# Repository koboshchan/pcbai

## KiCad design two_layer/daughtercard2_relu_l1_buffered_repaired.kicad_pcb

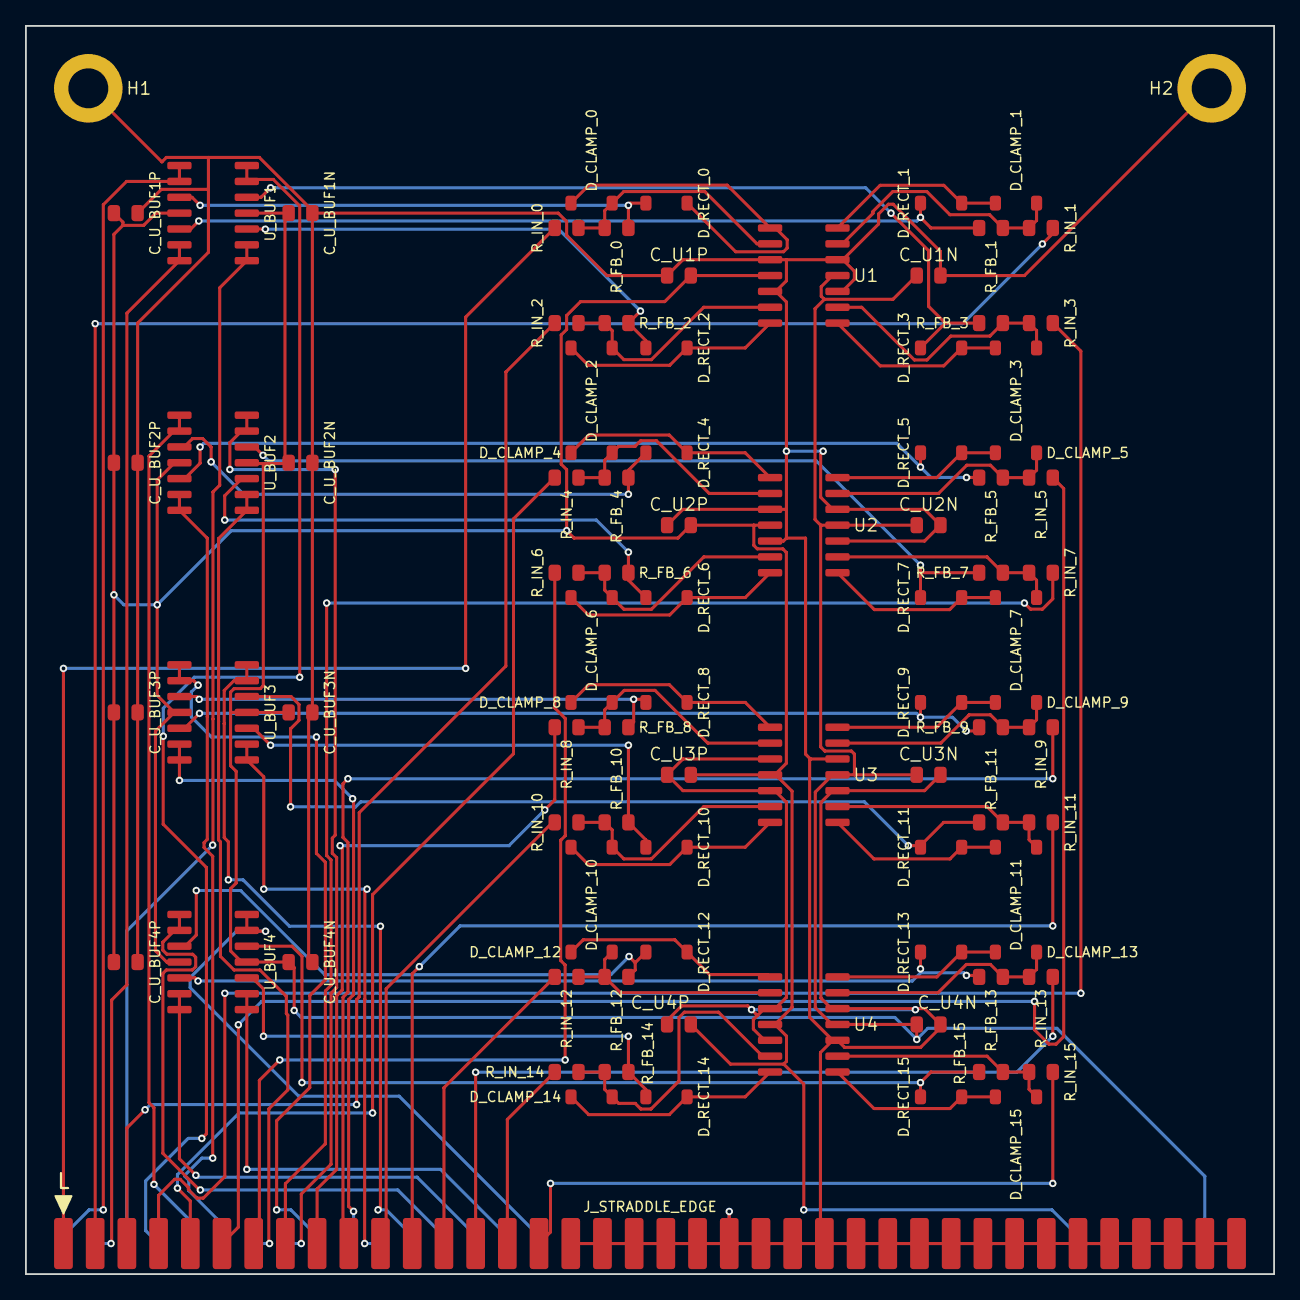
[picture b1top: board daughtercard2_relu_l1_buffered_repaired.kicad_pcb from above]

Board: 2 copper layers, 100.0 x 100.0 mm, 91 parts (0 on the bottom side), 83 nets.

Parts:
C_U1N, C_U1P, C_U2N, C_U2P, C_U3N, C_U3P, C_U4N, C_U4P: 0.1uF; C_0805_2012Metric
C_U_BUF1N, C_U_BUF1P, C_U_BUF2N, C_U_BUF2P, C_U_BUF3N, C_U_BUF3P, C_U_BUF4N, C_U_BUF4P: 0.1uF; C_0805_2012Metric
D_CLAMP_0, D_CLAMP_1, D_CLAMP_2, D_CLAMP_3, D_CLAMP_4, D_CLAMP_5, D_CLAMP_6, D_CLAMP_7, D_CLAMP_8, D_CLAMP_9, D_CLAMP_10, D_CLAMP_11, D_CLAMP_12, D_CLAMP_13, D_CLAMP_14, D_CLAMP_15: 1N4148W; D_SOD-123
D_RECT_0, D_RECT_1, D_RECT_2, D_RECT_3, D_RECT_4, D_RECT_5, D_RECT_6, D_RECT_7, D_RECT_8, D_RECT_9, D_RECT_10, D_RECT_11, D_RECT_12, D_RECT_13, D_RECT_14, D_RECT_15: 1N4148W; D_SOD-123
H1, H2: MountingHole; MountingHole_3.2mm_M3_Pad
J_STRADDLE_EDGE: PinHeader_2x38_Straddle; PinHeader_2x38_Straddle_P2.54mm
R_FB_0, R_FB_1, R_FB_2, R_FB_3, R_FB_4, R_FB_5, R_FB_6, R_FB_7, R_FB_8, R_FB_9, R_FB_10, R_FB_11, R_FB_12, R_FB_13, R_FB_14, R_FB_15: 10k; R_0805_2012Metric
R_IN_0, R_IN_1, R_IN_2, R_IN_3, R_IN_4, R_IN_5, R_IN_6, R_IN_7, R_IN_8, R_IN_9, R_IN_10, R_IN_11, R_IN_12, R_IN_13, R_IN_14, R_IN_15: 10k; R_0805_2012Metric
U1, U2, U3, U4: TL074; SOIC-14_3.9x8.7mm_P1.27mm
U_BUF1, U_BUF2, U_BUF3, U_BUF4: TL074; SOIC-14_3.9x8.7mm_P1.27mm

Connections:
+15V: C_U1P.2, C_U2P.2, C_U3P.2, C_U4P.2, C_U_BUF1P.1, C_U_BUF2P.1, C_U_BUF3P.1, C_U_BUF4P.1, J_STRADDLE_EDGE.B33, J_STRADDLE_EDGE.B34, U1.4, U2.4, U3.4, U4.4, U_BUF1.4, U_BUF2.4, U_BUF3.4, U_BUF4.4
-15V: C_U1N.1, C_U2N.1, C_U3N.1, C_U4N.1, C_U_BUF1N.1, C_U_BUF2N.1, C_U_BUF3N.1, C_U_BUF4N.1, J_STRADDLE_EDGE.B37, J_STRADDLE_EDGE.B38, U1.11, U2.11, U3.11, U4.11, U_BUF1.11, U_BUF2.11, U_BUF3.11, U_BUF4.11
ACT_0: J_STRADDLE_EDGE.B1, U_BUF1.1, U_BUF1.2
ACT_1: J_STRADDLE_EDGE.B2, U_BUF1.6, U_BUF1.7
ACT_2: J_STRADDLE_EDGE.B3, U_BUF1.8, U_BUF1.9
ACT_3: J_STRADDLE_EDGE.B4, U_BUF1.13, U_BUF1.14
ACT_4: J_STRADDLE_EDGE.B5, U_BUF2.1, U_BUF2.2
ACT_5: J_STRADDLE_EDGE.B6, U_BUF2.6, U_BUF2.7
ACT_6: J_STRADDLE_EDGE.B7, U_BUF2.8, U_BUF2.9
ACT_7: J_STRADDLE_EDGE.B8, U_BUF2.13, U_BUF2.14
ACT_8: J_STRADDLE_EDGE.B9, U_BUF3.1, U_BUF3.2
ACT_9: J_STRADDLE_EDGE.B10, U_BUF3.6, U_BUF3.7
ACT_10: J_STRADDLE_EDGE.B11, U_BUF3.8, U_BUF3.9
ACT_11: J_STRADDLE_EDGE.B12, U_BUF3.13, U_BUF3.14
ACT_12: J_STRADDLE_EDGE.B13, U_BUF4.1, U_BUF4.2
ACT_13: J_STRADDLE_EDGE.B14, U_BUF4.6, U_BUF4.7
ACT_14: J_STRADDLE_EDGE.B15, U_BUF4.8, U_BUF4.9
ACT_15: J_STRADDLE_EDGE.B16, U_BUF4.13, U_BUF4.14
GND: C_U1N.2, C_U1P.1, C_U2N.2, C_U2P.1, C_U3N.2, C_U3P.1, C_U4N.2, C_U4P.1, C_U_BUF1N.2, C_U_BUF1P.2, C_U_BUF2N.2, C_U_BUF2P.2, C_U_BUF3N.2, C_U_BUF3P.2, C_U_BUF4N.2, C_U_BUF4P.2, H1.1, H2.1, J_STRADDLE_EDGE.A17, J_STRADDLE_EDGE.A18, J_STRADDLE_EDGE.A19, J_STRADDLE_EDGE.A20, J_STRADDLE_EDGE.A21, J_STRADDLE_EDGE.A22, J_STRADDLE_EDGE.A23, J_STRADDLE_EDGE.A24, J_STRADDLE_EDGE.A25, J_STRADDLE_EDGE.A26, J_STRADDLE_EDGE.A27, J_STRADDLE_EDGE.A28, J_STRADDLE_EDGE.A29, J_STRADDLE_EDGE.A30, J_STRADDLE_EDGE.A31, J_STRADDLE_EDGE.A32, J_STRADDLE_EDGE.A33, J_STRADDLE_EDGE.A34, J_STRADDLE_EDGE.A35, J_STRADDLE_EDGE.A36, J_STRADDLE_EDGE.A37, J_STRADDLE_EDGE.A38, J_STRADDLE_EDGE.B17, J_STRADDLE_EDGE.B18, J_STRADDLE_EDGE.B19, J_STRADDLE_EDGE.B20, J_STRADDLE_EDGE.B21, J_STRADDLE_EDGE.B22, J_STRADDLE_EDGE.B23, J_STRADDLE_EDGE.B24, J_STRADDLE_EDGE.B25, J_STRADDLE_EDGE.B26, J_STRADDLE_EDGE.B27, J_STRADDLE_EDGE.B28, J_STRADDLE_EDGE.B29, J_STRADDLE_EDGE.B30, J_STRADDLE_EDGE.B31, J_STRADDLE_EDGE.B32, U1.3, U1.5, U1.10, U1.12, U2.3, U2.5, U2.10, U2.12, U3.3, U3.5, U3.10, U3.12, U4.3, U4.5, U4.10, U4.12
INV_RELU_0: D_CLAMP_0.2, R_FB_0.1, R_IN_0.2, U1.2
INV_RELU_1: D_CLAMP_1.2, R_FB_1.2, R_IN_1.1, U1.13
INV_RELU_2: D_CLAMP_2.2, R_FB_2.1, R_IN_2.2, U1.6
INV_RELU_3: D_CLAMP_3.2, R_FB_3.2, R_IN_3.1, U1.9
INV_RELU_4: D_CLAMP_4.2, R_FB_4.1, R_IN_4.2, U2.2
INV_RELU_5: D_CLAMP_5.2, R_FB_5.2, R_IN_5.1, U2.13
INV_RELU_6: D_CLAMP_6.2, R_FB_6.1, R_IN_6.2, U2.6
INV_RELU_7: D_CLAMP_7.2, R_FB_7.2, R_IN_7.1, U2.9
INV_RELU_8: D_CLAMP_8.2, R_FB_8.1, R_IN_8.2, U3.2
INV_RELU_9: D_CLAMP_9.2, R_FB_9.2, R_IN_9.1, U3.13
INV_RELU_10: D_CLAMP_10.2, R_FB_10.1, R_IN_10.2, U3.6
INV_RELU_11: D_CLAMP_11.2, R_FB_11.2, R_IN_11.1, U3.9
INV_RELU_12: D_CLAMP_12.2, R_FB_12.1, R_IN_12.2, U4.2
INV_RELU_13: D_CLAMP_13.2, R_FB_13.2, R_IN_13.1, U4.13
INV_RELU_14: D_CLAMP_14.2, R_FB_14.1, R_IN_14.2, U4.6
INV_RELU_15: D_CLAMP_15.2, R_FB_15.2, R_IN_15.1, U4.9
OP_OUT_0: D_CLAMP_0.1, D_RECT_0.2, U1.1
OP_OUT_1: D_CLAMP_1.1, D_RECT_1.2, U1.14
OP_OUT_2: D_CLAMP_2.1, D_RECT_2.2, U1.7
OP_OUT_3: D_CLAMP_3.1, D_RECT_3.2, U1.8
OP_OUT_4: D_CLAMP_4.1, D_RECT_4.2, U2.1
OP_OUT_5: D_CLAMP_5.1, D_RECT_5.2, U2.14
OP_OUT_6: D_CLAMP_6.1, D_RECT_6.2, U2.7
OP_OUT_7: D_CLAMP_7.1, D_RECT_7.2, U2.8
OP_OUT_8: D_CLAMP_8.1, D_RECT_8.2, U3.1
OP_OUT_9: D_CLAMP_9.1, D_RECT_9.2, U3.14
OP_OUT_10: D_CLAMP_10.1, D_RECT_10.2, U3.7
OP_OUT_11: D_CLAMP_11.1, D_RECT_11.2, U3.8
OP_OUT_12: D_CLAMP_12.1, D_RECT_12.2, U4.1
OP_OUT_13: D_CLAMP_13.1, D_RECT_13.2, U4.14
OP_OUT_14: D_CLAMP_14.1, D_RECT_14.2, U4.7
OP_OUT_15: D_CLAMP_15.1, D_RECT_15.2, U4.8
RECT_0: D_RECT_0.1, R_FB_0.2, U_BUF1.3
RECT_1: D_RECT_1.1, R_FB_1.1, U_BUF1.5
RECT_2: D_RECT_2.1, R_FB_2.2, U_BUF1.10
RECT_3: D_RECT_3.1, R_FB_3.1, U_BUF1.12
RECT_4: D_RECT_4.1, R_FB_4.2, U_BUF2.3
RECT_5: D_RECT_5.1, R_FB_5.1, U_BUF2.5
RECT_6: D_RECT_6.1, R_FB_6.2, U_BUF2.10
RECT_7: D_RECT_7.1, R_FB_7.1, U_BUF2.12
RECT_8: D_RECT_8.1, R_FB_8.2, U_BUF3.3
RECT_9: D_RECT_9.1, R_FB_9.1, U_BUF3.5
RECT_10: D_RECT_10.1, R_FB_10.2, U_BUF3.10
RECT_11: D_RECT_11.1, R_FB_11.1, U_BUF3.12
RECT_12: D_RECT_12.1, R_FB_12.2, U_BUF4.3
RECT_13: D_RECT_13.1, R_FB_13.1, U_BUF4.5
RECT_14: D_RECT_14.1, R_FB_14.2, U_BUF4.10
RECT_15: D_RECT_15.1, R_FB_15.1, U_BUF4.12
V_SUM_0: J_STRADDLE_EDGE.A1, R_IN_0.1
V_SUM_1: J_STRADDLE_EDGE.A2, R_IN_1.2
V_SUM_2: J_STRADDLE_EDGE.A3, R_IN_2.1
V_SUM_3: J_STRADDLE_EDGE.A4, R_IN_3.2
V_SUM_4: J_STRADDLE_EDGE.A5, R_IN_4.1
V_SUM_5: J_STRADDLE_EDGE.A6, R_IN_5.2
V_SUM_6: J_STRADDLE_EDGE.A7, R_IN_6.1
V_SUM_7: J_STRADDLE_EDGE.A8, R_IN_7.2
V_SUM_8: J_STRADDLE_EDGE.A9, R_IN_8.1
V_SUM_9: J_STRADDLE_EDGE.A10, R_IN_9.2
V_SUM_10: J_STRADDLE_EDGE.A11, R_IN_10.1
V_SUM_11: J_STRADDLE_EDGE.A12, R_IN_11.2
V_SUM_12: J_STRADDLE_EDGE.A13, R_IN_12.1
V_SUM_13: J_STRADDLE_EDGE.A14, R_IN_13.2
V_SUM_14: J_STRADDLE_EDGE.A15, R_IN_14.1
V_SUM_15: J_STRADDLE_EDGE.A16, R_IN_15.2

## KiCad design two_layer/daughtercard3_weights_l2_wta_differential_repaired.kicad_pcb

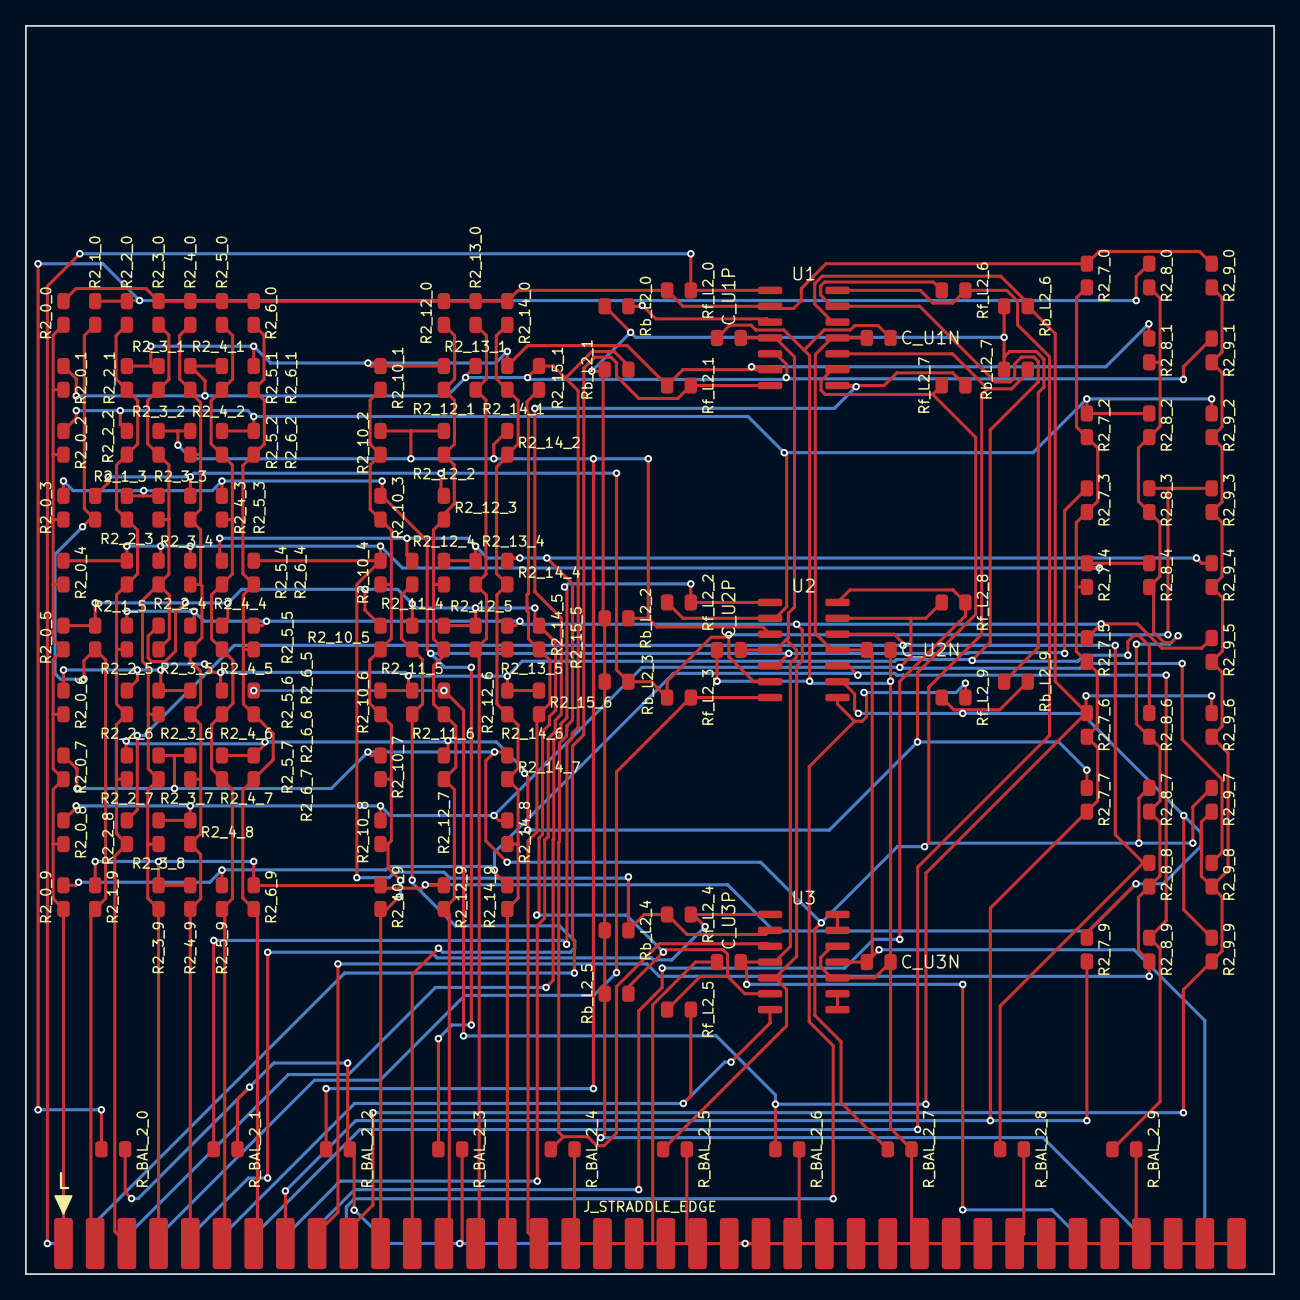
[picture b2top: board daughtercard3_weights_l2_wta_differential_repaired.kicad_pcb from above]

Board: 2 copper layers, 100.0 x 100.0 mm, 163 parts (0 on the bottom side), 52 nets.

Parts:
C_U1N, C_U1P, C_U2N, C_U2P, C_U3N, C_U3P: 0.1uF; C_0805_2012Metric
J_STRADDLE_EDGE: PinHeader_2x38_Straddle; PinHeader_2x38_Straddle_P2.54mm
R2_0_0, R2_3_2, R2_8_3, R2_9_1, R2_10_6: 91k; R_0805_2012Metric
R2_0_1, R2_3_0, R2_6_5, R2_7_4, R2_9_0, R2_14_1: 100k; R_0805_2012Metric
R2_0_2: 1.6M; R_0805_2012Metric
R2_0_3, R2_1_3, R2_5_4, R2_6_2, R2_7_6, R2_10_5, R2_10_8, R2_13_0, R2_14_0: 220k; R_0805_2012Metric
R2_0_4, R2_2_7, R2_5_3, R2_7_3, R2_8_6, R2_9_3, R2_13_5: 270k; R_0805_2012Metric
R2_0_5, R2_0_6, R2_5_0: 56k; R_0805_2012Metric
R2_0_7, R2_3_5: 470k; R_0805_2012Metric
R2_0_8, R2_1_9, R2_5_5, R2_5_9, R2_9_2, R2_9_4, R2_9_8, R2_10_7, R2_11_4, R2_11_6, R2_12_6: 180k; R_0805_2012Metric
R2_0_9, R2_2_2, R2_4_5, R2_4_6, R2_8_9, R2_12_5, R2_14_9: 300k; R_0805_2012Metric
R2_1_0, R2_2_3, R2_2_4, R2_8_0, R2_10_3, R2_11_5, R2_14_7, R2_15_5: 240k; R_0805_2012Metric
R2_1_5, R2_5_1: 82k; R_0805_2012Metric
R2_2_0, R2_10_9, R2_14_8: 110k; R_0805_2012Metric
R2_2_1: 51k; R_0805_2012Metric
R2_2_5, R2_3_3, R2_3_7, R2_15_6: 360k; R_0805_2012Metric
R2_2_6, R2_4_9: 430k; R_0805_2012Metric
R2_2_8: 5.1M; R_0805_2012Metric
R2_3_1, R2_6_9, R2_7_7, R2_9_9, R2_10_2, R2_13_4: 150k; R_0805_2012Metric
R2_3_4, R2_3_9, R2_5_2, R2_14_4: 130k; R_0805_2012Metric
R2_3_6, R2_5_6, R2_6_4, R2_7_2, R2_7_5, R2_10_1: 68k; R_0805_2012Metric
R2_3_8, R2_5_7, R2_6_0, R2_6_6, R2_8_2, R2_12_1, R2_12_4, R2_14_6: 200k; R_0805_2012Metric
R2_4_0, R2_9_5: 1M; R_0805_2012Metric
R2_4_1, R2_4_4, R2_8_8: 120k; R_0805_2012Metric
R2_4_2: 680k; R_0805_2012Metric
R2_4_3, R2_14_2: 750k; R_0805_2012Metric
R2_4_7, R2_12_3: 390k; R_0805_2012Metric
R2_4_8: 62k; R_0805_2012Metric
R2_6_1, R2_12_7: 43k; R_0805_2012Metric
R2_6_7, R2_8_7: 330k; R_0805_2012Metric
R2_7_0, R2_7_9: 75k; R_0805_2012Metric
R2_8_1, R2_12_9, R2_15_1: 160k; R_0805_2012Metric
R2_8_4, R2_9_6, R2_9_7: 620k; R_0805_2012Metric
R2_10_4: 33k; R_0805_2012Metric
R2_12_0: 510k; R_0805_2012Metric
R2_12_2: 1.1M; R_0805_2012Metric
R2_13_1: 820k; R_0805_2012Metric
R2_14_5: 2.7M; R_0805_2012Metric
R_BAL_2_0: 14.7k; R_0805_2012Metric
R_BAL_2_1: 24.9k; R_0805_2012Metric
R_BAL_2_2: 35.7k; R_0805_2012Metric
R_BAL_2_3: 61.9k; R_0805_2012Metric
R_BAL_2_4: 17.4k; R_0805_2012Metric
R_BAL_2_5: 28k; R_0805_2012Metric
R_BAL_2_6: 14.3k; R_0805_2012Metric
R_BAL_2_7: 34k; R_0805_2012Metric
R_BAL_2_8: 21k; R_0805_2012Metric
R_BAL_2_9: 18.2k; R_0805_2012Metric
Rb_L2_0: 270k; R_0805_2012Metric
Rb_L2_1, Rb_L2_3: 160k; R_0805_2012Metric
Rb_L2_2, Rb_L2_4: 560k; R_0805_2012Metric
Rb_L2_5: 2M; R_0805_2012Metric
Rb_L2_6: 240k; R_0805_2012Metric
Rb_L2_7: 3.9M; R_0805_2012Metric
Rb_L2_9: 360k; R_0805_2012Metric
Rf_L2_0, Rf_L2_1, Rf_L2_2, Rf_L2_3, Rf_L2_4, Rf_L2_5, Rf_L2_6, Rf_L2_7, Rf_L2_8, Rf_L2_9: 100k; R_0805_2012Metric
U1, U2, U3: TL074; SOIC-14_3.9x8.7mm_P1.27mm

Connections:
+5V_REF: J_STRADDLE_EDGE.B35, Rb_L2_0.1, Rb_L2_1.1, Rb_L2_2.1, Rb_L2_3.1, Rb_L2_4.1, Rb_L2_5.1, Rb_L2_6.1, Rb_L2_7.1, Rb_L2_9.1
+15V: C_U1P.2, C_U2P.2, C_U3P.2, J_STRADDLE_EDGE.B33, J_STRADDLE_EDGE.B34, U1.4, U2.4, U3.4
-15V: C_U1N.1, C_U2N.1, C_U3N.1, J_STRADDLE_EDGE.B37, J_STRADDLE_EDGE.B38, U1.11, U2.11, U3.11
ACT_0: J_STRADDLE_EDGE.A1, R2_0_0.1, R2_0_1.1, R2_0_2.1, R2_0_3.1, R2_0_4.1, R2_0_5.1, R2_0_6.1, R2_0_7.1, R2_0_8.1, R2_0_9.1
ACT_1: J_STRADDLE_EDGE.A2, R2_1_0.1, R2_1_3.1, R2_1_5.1, R2_1_9.1
ACT_2: J_STRADDLE_EDGE.A3, R2_2_0.1, R2_2_1.1, R2_2_2.1, R2_2_3.1, R2_2_4.1, R2_2_5.1, R2_2_6.1, R2_2_7.1, R2_2_8.1
ACT_3: J_STRADDLE_EDGE.A4, R2_3_0.1, R2_3_1.1, R2_3_2.1, R2_3_3.1, R2_3_4.1, R2_3_5.1, R2_3_6.1, R2_3_7.1, R2_3_8.1, R2_3_9.1
ACT_4: J_STRADDLE_EDGE.A5, R2_4_0.1, R2_4_1.1, R2_4_2.1, R2_4_3.1, R2_4_4.1, R2_4_5.1, R2_4_6.1, R2_4_7.1, R2_4_8.1, R2_4_9.1
ACT_5: J_STRADDLE_EDGE.A6, R2_5_0.1, R2_5_1.1, R2_5_2.1, R2_5_3.1, R2_5_4.1, R2_5_5.1, R2_5_6.1, R2_5_7.1, R2_5_9.1
ACT_6: J_STRADDLE_EDGE.A7, R2_6_0.1, R2_6_1.1, R2_6_2.1, R2_6_4.1, R2_6_5.1, R2_6_6.1, R2_6_7.1, R2_6_9.1
ACT_7: J_STRADDLE_EDGE.A8, R2_7_0.1, R2_7_2.1, R2_7_3.1, R2_7_4.1, R2_7_5.1, R2_7_6.1, R2_7_7.1, R2_7_9.1
ACT_8: J_STRADDLE_EDGE.A9, R2_8_0.1, R2_8_1.1, R2_8_2.1, R2_8_3.1, R2_8_4.1, R2_8_6.1, R2_8_7.1, R2_8_8.1, R2_8_9.1
ACT_9: J_STRADDLE_EDGE.A10, R2_9_0.1, R2_9_1.1, R2_9_2.1, R2_9_3.1, R2_9_4.1, R2_9_5.1, R2_9_6.1, R2_9_7.1, R2_9_8.1, R2_9_9.1
ACT_10: J_STRADDLE_EDGE.A11, R2_10_1.1, R2_10_2.1, R2_10_3.1, R2_10_4.1, R2_10_5.1, R2_10_6.1, R2_10_7.1, R2_10_8.1, R2_10_9.1
ACT_11: J_STRADDLE_EDGE.A12, R2_11_4.1, R2_11_5.1, R2_11_6.1
ACT_12: J_STRADDLE_EDGE.A13, R2_12_0.1, R2_12_1.1, R2_12_2.1, R2_12_3.1, R2_12_4.1, R2_12_5.1, R2_12_6.1, R2_12_7.1, R2_12_9.1
ACT_13: J_STRADDLE_EDGE.A14, R2_13_0.1, R2_13_1.1, R2_13_4.1, R2_13_5.1
ACT_14: J_STRADDLE_EDGE.A15, R2_14_0.1, R2_14_1.1, R2_14_2.1, R2_14_4.1, R2_14_5.1, R2_14_6.1, R2_14_7.1, R2_14_8.1, R2_14_9.1
ACT_15: J_STRADDLE_EDGE.A16, R2_15_1.1, R2_15_5.1, R2_15_6.1
GND: C_U1N.2, C_U1P.1, C_U2N.2, C_U2P.1, C_U3N.2, C_U3P.1, J_STRADDLE_EDGE.A17, J_STRADDLE_EDGE.A18, J_STRADDLE_EDGE.A19, J_STRADDLE_EDGE.A20, J_STRADDLE_EDGE.A21, J_STRADDLE_EDGE.A22, J_STRADDLE_EDGE.A23, J_STRADDLE_EDGE.A24, J_STRADDLE_EDGE.A25, J_STRADDLE_EDGE.A26, J_STRADDLE_EDGE.A27, J_STRADDLE_EDGE.A28, J_STRADDLE_EDGE.A29, J_STRADDLE_EDGE.A30, J_STRADDLE_EDGE.A31, J_STRADDLE_EDGE.A32, J_STRADDLE_EDGE.A33, J_STRADDLE_EDGE.A34, J_STRADDLE_EDGE.A35, J_STRADDLE_EDGE.A36, J_STRADDLE_EDGE.A37, J_STRADDLE_EDGE.A38, J_STRADDLE_EDGE.B11, J_STRADDLE_EDGE.B12, J_STRADDLE_EDGE.B13, J_STRADDLE_EDGE.B14, J_STRADDLE_EDGE.B15, J_STRADDLE_EDGE.B16, J_STRADDLE_EDGE.B17, J_STRADDLE_EDGE.B18, J_STRADDLE_EDGE.B19, J_STRADDLE_EDGE.B20, J_STRADDLE_EDGE.B21, J_STRADDLE_EDGE.B22, J_STRADDLE_EDGE.B23, J_STRADDLE_EDGE.B24, J_STRADDLE_EDGE.B25, J_STRADDLE_EDGE.B26, J_STRADDLE_EDGE.B27, J_STRADDLE_EDGE.B28, J_STRADDLE_EDGE.B29, J_STRADDLE_EDGE.B30, J_STRADDLE_EDGE.B31, J_STRADDLE_EDGE.B32, R_BAL_2_0.2, R_BAL_2_1.2, R_BAL_2_2.2, R_BAL_2_3.2, R_BAL_2_4.2, R_BAL_2_5.2, R_BAL_2_6.2, R_BAL_2_7.2, R_BAL_2_8.2, R_BAL_2_9.2, U3.10, U3.12
INV_L2_0: R2_0_0.2, R2_3_0.2, R2_4_0.2, R2_5_0.2, R2_6_0.2, R2_7_0.2, R2_9_0.2, R2_12_0.2, R2_13_0.2, R2_14_0.2, Rf_L2_0.1, U1.2
INV_L2_1: R2_2_1.2, R2_3_1.2, R2_6_1.2, R2_8_1.2, R2_10_1.2, R2_12_1.2, R2_14_1.2, Rf_L2_1.1, U1.6
INV_L2_2: R2_0_2.2, R2_2_2.2, R2_5_2.2, R2_6_2.2, R2_7_2.2, R2_8_2.2, R2_9_2.2, Rf_L2_2.1, U2.2
INV_L2_3: R2_1_3.2, R2_4_3.2, R2_8_3.2, R2_9_3.2, R2_12_3.2, Rb_L2_3.2, Rf_L2_3.1, U2.6
INV_L2_4: R2_0_4.2, R2_2_4.2, R2_3_4.2, R2_4_4.2, R2_6_4.2, R2_7_4.2, R2_8_4.2, R2_10_4.2, Rb_L2_4.2, Rf_L2_4.1, U3.2
INV_L2_5: R2_0_5.2, R2_1_5.2, R2_3_5.2, R2_5_5.2, R2_10_5.2, R2_11_5.2, R2_12_5.2, R2_13_5.2, R2_15_5.2, Rb_L2_5.2, Rf_L2_5.1, U3.6
INV_L2_6: R2_0_6.2, R2_2_6.2, R2_3_6.2, R2_4_6.2, R2_5_6.2, R2_8_6.2, R2_10_6.2, R2_11_6.2, R2_14_6.2, R2_15_6.2, Rf_L2_6.1, U1.13
INV_L2_7: R2_2_7.2, R2_5_7.2, R2_6_7.2, R2_7_7.2, R2_12_7.2, Rf_L2_7.1, U1.9
INV_L2_8: R2_0_8.2, R2_3_8.2, R2_4_8.2, R2_9_8.2, R2_10_8.2, R2_14_8.2, Rf_L2_8.1, U2.13
INV_L2_9: R2_1_9.2, R2_3_9.2, R2_4_9.2, R2_6_9.2, R2_7_9.2, R2_9_9.2, R2_10_9.2, R2_12_9.2, Rb_L2_9.2, Rf_L2_9.1, U2.9
NC_U3_8: U3.8, U3.9
NC_U3_14: U3.13, U3.14
POS_L2_0: R2_1_0.2, R2_2_0.2, R2_8_0.2, R_BAL_2_0.1, Rb_L2_0.2, U1.3
POS_L2_1: R2_0_1.2, R2_4_1.2, R2_5_1.2, R2_9_1.2, R2_13_1.2, R2_15_1.2, R_BAL_2_1.1, Rb_L2_1.2, U1.5
POS_L2_2: R2_3_2.2, R2_4_2.2, R2_10_2.2, R2_12_2.2, R2_14_2.2, R_BAL_2_2.1, Rb_L2_2.2, U2.3
POS_L2_3: R2_0_3.2, R2_2_3.2, R2_3_3.2, R2_5_3.2, R2_7_3.2, R2_10_3.2, R_BAL_2_3.1, U2.5
POS_L2_4: R2_5_4.2, R2_9_4.2, R2_11_4.2, R2_12_4.2, R2_13_4.2, R2_14_4.2, R_BAL_2_4.1, U3.3
POS_L2_5: R2_2_5.2, R2_4_5.2, R2_6_5.2, R2_7_5.2, R2_9_5.2, R2_14_5.2, R_BAL_2_5.1, U3.5
POS_L2_6: R2_6_6.2, R2_7_6.2, R2_9_6.2, R2_12_6.2, R_BAL_2_6.1, Rb_L2_6.2, U1.12
POS_L2_7: R2_0_7.2, R2_3_7.2, R2_4_7.2, R2_8_7.2, R2_9_7.2, R2_10_7.2, R2_14_7.2, R_BAL_2_7.1, Rb_L2_7.2, U1.10
POS_L2_8: R2_2_8.2, R2_8_8.2, R_BAL_2_8.1, U2.12
POS_L2_9: R2_0_9.2, R2_5_9.2, R2_8_9.2, R2_14_9.2, R_BAL_2_9.1, U2.10
SCORE_0: J_STRADDLE_EDGE.B1, Rf_L2_0.2, U1.1
SCORE_1: J_STRADDLE_EDGE.B2, Rf_L2_1.2, U1.7
SCORE_2: J_STRADDLE_EDGE.B3, Rf_L2_2.2, U2.1
SCORE_3: J_STRADDLE_EDGE.B4, Rf_L2_3.2, U2.7
SCORE_4: J_STRADDLE_EDGE.B5, Rf_L2_4.2, U3.1
SCORE_5: J_STRADDLE_EDGE.B6, Rf_L2_5.2, U3.7
SCORE_6: J_STRADDLE_EDGE.B7, Rf_L2_6.2, U1.14
SCORE_7: J_STRADDLE_EDGE.B8, Rf_L2_7.2, U1.8
SCORE_8: J_STRADDLE_EDGE.B9, Rf_L2_8.2, U2.14
SCORE_9: J_STRADDLE_EDGE.B10, Rf_L2_9.2, U2.8

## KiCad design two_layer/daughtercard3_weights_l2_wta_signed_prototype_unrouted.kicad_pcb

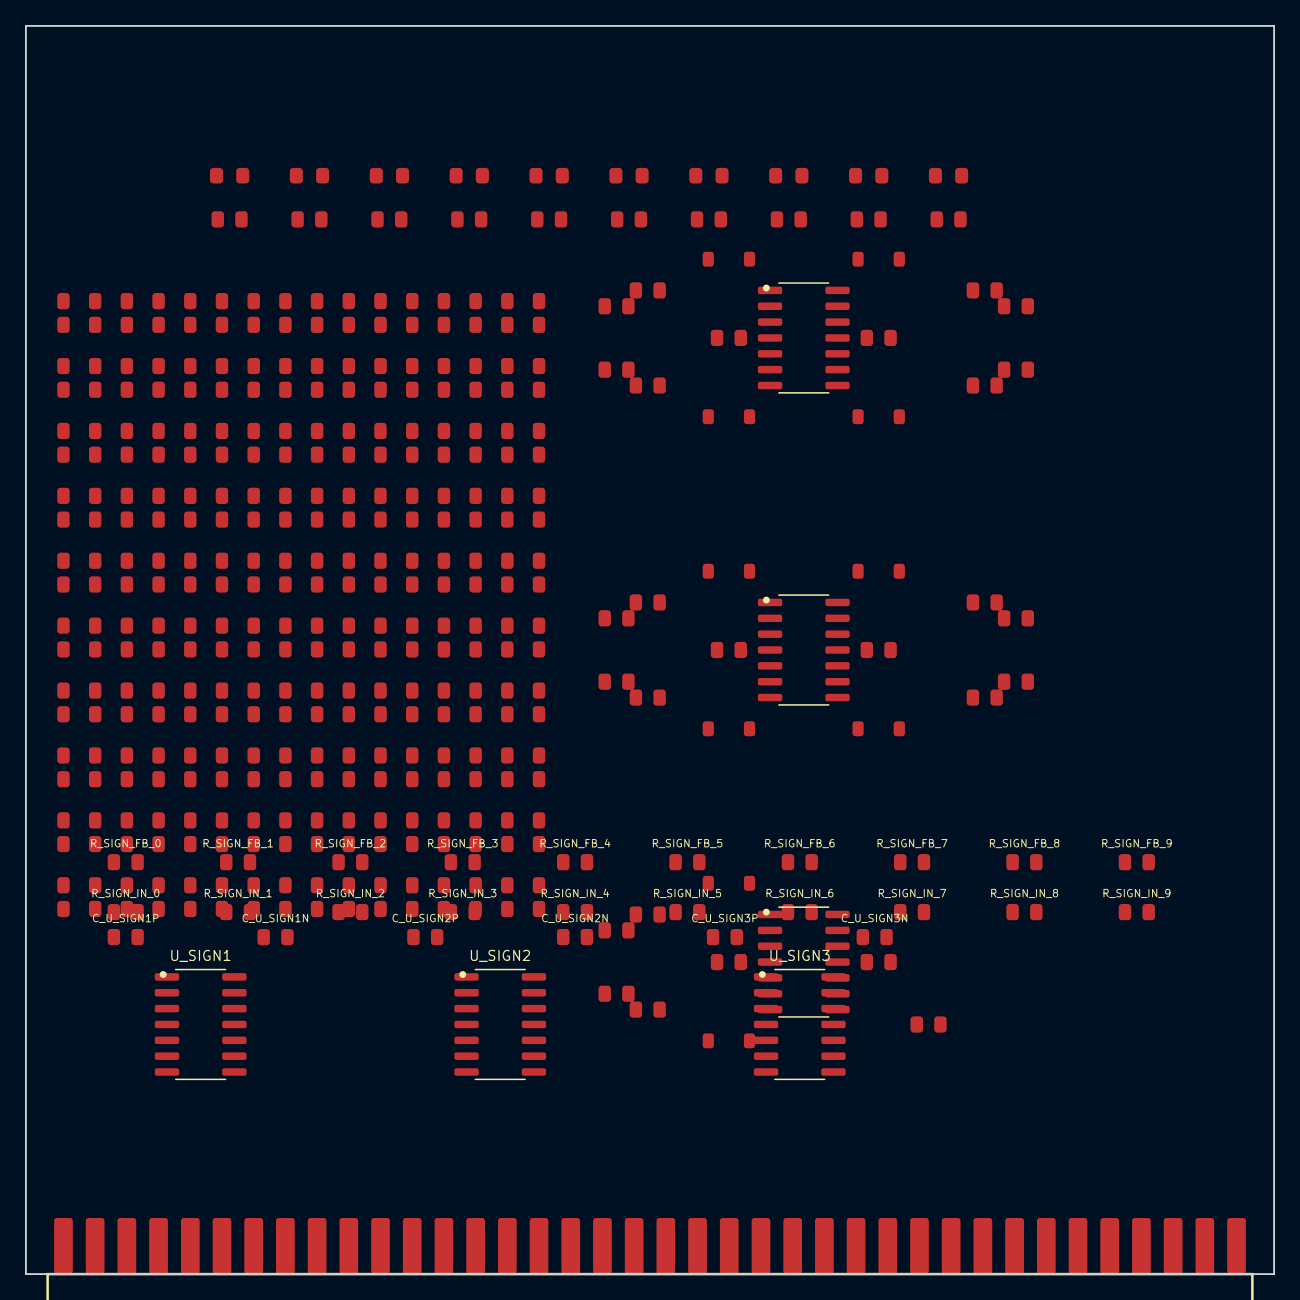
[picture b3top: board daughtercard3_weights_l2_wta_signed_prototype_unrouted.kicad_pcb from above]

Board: 2 copper layers, 100.0 x 100.0 mm, 250 parts (0 on the bottom side), 76 nets, no tracks yet.

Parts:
C_U1N, C_U1P, C_U2N, C_U2P, C_U3N, C_U3P: 0.1uF; C_0805_2012Metric
C_U_SIGN1N, C_U_SIGN1P, C_U_SIGN2N, C_U_SIGN2P, C_U_SIGN3N, C_U_SIGN3P: 0.1uF; C_0805_2012Metric
D_LED_0: Digit_0; LED_0805_2012Metric
D_LED_1: Digit_1; LED_0805_2012Metric
D_LED_2: Digit_2; LED_0805_2012Metric
D_LED_3: Digit_3; LED_0805_2012Metric
D_LED_4: Digit_4; LED_0805_2012Metric
D_LED_5: Digit_5; LED_0805_2012Metric
D_LED_6: Digit_6; LED_0805_2012Metric
D_LED_7: Digit_7; LED_0805_2012Metric
D_LED_8: Digit_8; LED_0805_2012Metric
D_LED_9: Digit_9; LED_0805_2012Metric
D_WTA_0, D_WTA_1, D_WTA_2, D_WTA_3, D_WTA_4, D_WTA_5, D_WTA_6, D_WTA_7, D_WTA_8, D_WTA_9: 1N4148; D_SOD-123
J_STRADDLE_EDGE: PinHeader_2x38_Straddle; PinHeader_2x38_Straddle_P2.54mm
R2_0_0, R2_0_1, R2_2_0, R2_3_2, R2_6_5, R2_7_0, R2_8_3, R2_8_8, R2_9_0, R2_10_9: 12k; R_0805_2012Metric
R2_0_2, R2_1_2, R2_1_7, R2_11_1, R2_15_2, R2_15_9: 300k; R_0805_2012Metric
R2_0_3, R2_0_7, R2_0_8, R2_0_9, R2_1_5, R2_2_2, R2_2_5, R2_2_6, R2_2_7, R2_4_7, R2_5_7, R2_7_3, R2_8_0, R2_8_7, R2_8_9, R2_9_6, R2_9_8, R2_12_5, R2_13_4, R2_14_6, R2_14_9: 33k; R_0805_2012Metric
R2_0_4, R2_2_3, R2_3_1, R2_3_4, R2_4_4, R2_4_5, R2_5_3, R2_5_5, R2_6_2, R2_6_9, R2_7_7, R2_8_2, R2_9_2, R2_10_3, R2_12_1, R2_12_4, R2_12_9, R2_14_7: 22k; R_0805_2012Metric
R2_0_5, R2_0_6, R2_2_1, R2_5_1, R2_5_6, R2_7_2, R2_7_5, R2_7_9: 7.5k; R_0805_2012Metric
R2_1_0, R2_1_6, R2_1_8, R2_2_8, R2_3_5, R2_4_2, R2_9_5, R2_11_2, R2_11_7, R2_11_9, R2_13_5, R2_13_6, R2_13_7, R2_15_3, R2_15_7, R2_15_8: 75k; R_0805_2012Metric
R2_1_1, R2_1_3, R2_1_9, R2_2_4, R2_10_5, R2_11_4, R2_14_0, R2_15_4: 51k; R_0805_2012Metric
R2_1_4, R2_2_9, R2_5_8, R2_8_4, R2_11_0, R2_11_5, R2_11_6, R2_11_8, R2_12_0, R2_12_8, R2_13_1, R2_13_8, R2_14_5, R2_15_0, R2_15_6: 100k; R_0805_2012Metric
R2_3_0, R2_4_1, R2_10_6, R2_14_1, R2_14_4, R2_14_8: 15k; R_0805_2012Metric
R2_3_3, R2_3_7, R2_3_8, R2_4_6, R2_6_6, R2_6_7, R2_7_1, R2_9_3, R2_10_8, R2_12_3, R2_13_2, R2_14_2: 43k; R_0805_2012Metric
R2_3_6, R2_4_8, R2_6_4, R2_7_4, R2_9_1, R2_10_1: 10k; R_0805_2012Metric
R2_3_9, R2_5_2, R2_5_4, R2_5_9, R2_7_6, R2_8_6, R2_10_7, R2_12_6: 20k; R_0805_2012Metric
R2_4_0, R2_4_3, R2_14_3: 390k; R_0805_2012Metric
R2_4_9, R2_7_8, R2_11_3, R2_12_2, R2_13_3, R2_13_9, R2_15_1: 200k; R_0805_2012Metric
R2_5_0, R2_6_1: 5.6k; R_0805_2012Metric
R2_6_0, R2_8_1, R2_9_4, R2_9_9, R2_10_2: 18k; R_0805_2012Metric
R2_6_3, R2_9_7: 47k; R_0805_2012Metric
R2_6_8, R2_13_0: 680k; R_0805_2012Metric
R2_8_5, R2_15_5: 1M; R_0805_2012Metric
R2_10_0: 10M; R_0805_2012Metric
R2_10_4: 3.3k; R_0805_2012Metric
R2_12_7: 5.1k; R_0805_2012Metric
R_LED_0, R_LED_1, R_LED_2, R_LED_3, R_LED_4, R_LED_5, R_LED_6, R_LED_7, R_LED_8, R_LED_9: 1k; R_0805_2012Metric
R_SIGN_FB_0, R_SIGN_FB_1, R_SIGN_FB_2, R_SIGN_FB_3, R_SIGN_FB_4, R_SIGN_FB_5, R_SIGN_FB_6, R_SIGN_FB_7, R_SIGN_FB_8, R_SIGN_FB_9: 1.2k; R_0805_2012Metric
R_SIGN_IN_0, R_SIGN_IN_1, R_SIGN_IN_2, R_SIGN_IN_3, R_SIGN_IN_4, R_SIGN_IN_5, R_SIGN_IN_6, R_SIGN_IN_7, R_SIGN_IN_8, R_SIGN_IN_9: 1.2k; R_0805_2012Metric
R_WTA: 10k; R_0805_2012Metric
Rb_L2_0, Rb_L2_6: 33k; R_0805_2012Metric
Rb_L2_1, Rb_L2_3: 18k; R_0805_2012Metric
Rb_L2_2, Rb_L2_4: 75k; R_0805_2012Metric
Rb_L2_5, Rb_L2_7: 100k; R_0805_2012Metric
Rb_L2_8: 470k; R_0805_2012Metric
Rb_L2_9: 43k; R_0805_2012Metric
Rf_L2_0, Rf_L2_1, Rf_L2_2, Rf_L2_3, Rf_L2_4, Rf_L2_5, Rf_L2_6, Rf_L2_7, Rf_L2_8, Rf_L2_9: 10k; R_0805_2012Metric
U1, U2, U3: TL074; SOIC-14_3.9x8.7mm_P1.27mm
U_SIGN1, U_SIGN2, U_SIGN3: TL074; SOIC-14_3.9x8.7mm_P1.27mm

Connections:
+5V_REF: J_STRADDLE_EDGE.B35, Rb_L2_3.1, Rb_L2_4.1, Rb_L2_5.1, Rb_L2_9.2
+12V: C_U1P.2, C_U2P.2, C_U3P.2, C_U_SIGN1P.1, C_U_SIGN2P.1, C_U_SIGN3P.1, J_STRADDLE_EDGE.B33, J_STRADDLE_EDGE.B34, U1.4, U2.4, U3.4, U_SIGN1.4, U_SIGN2.4, U_SIGN3.4
-5V_REF: J_STRADDLE_EDGE.B36, Rb_L2_0.1, Rb_L2_1.1, Rb_L2_2.1, Rb_L2_6.2, Rb_L2_7.2, Rb_L2_8.2
-12V: C_U1N.1, C_U2N.1, C_U3N.1, C_U_SIGN1N.1, C_U_SIGN2N.1, C_U_SIGN3N.1, J_STRADDLE_EDGE.B37, J_STRADDLE_EDGE.B38, R_WTA.2, U1.11, U2.11, U3.11, U_SIGN1.11, U_SIGN2.11, U_SIGN3.11
ACT_0: J_STRADDLE_EDGE.A1, R2_0_0.1, R2_0_1.1, R2_0_2.1, R2_0_3.1, R2_0_4.1, R2_0_5.1, R2_0_6.1, R2_0_7.1, R2_0_8.1, R2_0_9.1
ACT_1: J_STRADDLE_EDGE.A2, R2_1_0.1, R2_1_1.1, R2_1_2.1, R2_1_3.1, R2_1_4.1, R2_1_5.1, R2_1_6.1, R2_1_7.1, R2_1_8.1, R2_1_9.1
ACT_2: J_STRADDLE_EDGE.A3, R2_2_0.1, R2_2_1.1, R2_2_2.1, R2_2_3.1, R2_2_4.1, R2_2_5.1, R2_2_6.1, R2_2_7.1, R2_2_8.1, R2_2_9.1
ACT_3: J_STRADDLE_EDGE.A4, R2_3_0.1, R2_3_1.1, R2_3_2.1, R2_3_3.1, R2_3_4.1, R2_3_5.1, R2_3_6.1, R2_3_7.1, R2_3_8.1, R2_3_9.1
ACT_4: J_STRADDLE_EDGE.A5, R2_4_0.1, R2_4_1.1, R2_4_2.1, R2_4_3.1, R2_4_4.1, R2_4_5.1, R2_4_6.1, R2_4_7.1, R2_4_8.1, R2_4_9.1
ACT_5: J_STRADDLE_EDGE.A6, R2_5_0.1, R2_5_1.1, R2_5_2.1, R2_5_3.1, R2_5_4.1, R2_5_5.1, R2_5_6.1, R2_5_7.1, R2_5_8.1, R2_5_9.1
ACT_6: J_STRADDLE_EDGE.A7, R2_6_0.1, R2_6_1.1, R2_6_2.1, R2_6_3.1, R2_6_4.1, R2_6_5.1, R2_6_6.1, R2_6_7.1, R2_6_8.1, R2_6_9.1
ACT_7: J_STRADDLE_EDGE.A8, R2_7_0.1, R2_7_1.1, R2_7_2.1, R2_7_3.1, R2_7_4.1, R2_7_5.1, R2_7_6.1, R2_7_7.1, R2_7_8.1, R2_7_9.1
ACT_8: J_STRADDLE_EDGE.A9, R2_8_0.1, R2_8_1.1, R2_8_2.1, R2_8_3.1, R2_8_4.1, R2_8_5.1, R2_8_6.1, R2_8_7.1, R2_8_8.1, R2_8_9.1
ACT_9: J_STRADDLE_EDGE.A10, R2_9_0.1, R2_9_1.1, R2_9_2.1, R2_9_3.1, R2_9_4.1, R2_9_5.1, R2_9_6.1, R2_9_7.1, R2_9_8.1, R2_9_9.1
ACT_10: J_STRADDLE_EDGE.A11, R2_10_0.1, R2_10_1.1, R2_10_2.1, R2_10_3.1, R2_10_4.1, R2_10_5.1, R2_10_6.1, R2_10_7.1, R2_10_8.1, R2_10_9.1
ACT_11: J_STRADDLE_EDGE.A12, R2_11_0.1, R2_11_1.1, R2_11_2.1, R2_11_3.1, R2_11_4.1, R2_11_5.1, R2_11_6.1, R2_11_7.1, R2_11_8.1, R2_11_9.1
ACT_12: J_STRADDLE_EDGE.A13, R2_12_0.1, R2_12_1.1, R2_12_2.1, R2_12_3.1, R2_12_4.1, R2_12_5.1, R2_12_6.1, R2_12_7.1, R2_12_8.1, R2_12_9.1
ACT_13: J_STRADDLE_EDGE.A14, R2_13_0.1, R2_13_1.1, R2_13_2.1, R2_13_3.1, R2_13_4.1, R2_13_5.1, R2_13_6.1, R2_13_7.1, R2_13_8.1, R2_13_9.1
ACT_14: J_STRADDLE_EDGE.A15, R2_14_0.1, R2_14_1.1, R2_14_2.1, R2_14_3.1, R2_14_4.1, R2_14_5.1, R2_14_6.1, R2_14_7.1, R2_14_8.1, R2_14_9.1
ACT_15: J_STRADDLE_EDGE.A16, R2_15_0.1, R2_15_1.1, R2_15_2.1, R2_15_3.1, R2_15_4.1, R2_15_5.1, R2_15_6.1, R2_15_7.1, R2_15_8.1, R2_15_9.1
GND: C_U1N.2, C_U1P.1, C_U2N.2, C_U2P.1, C_U3N.2, C_U3P.1, C_U_SIGN1N.2, C_U_SIGN1P.2, C_U_SIGN2N.2, C_U_SIGN2P.2, C_U_SIGN3N.2, C_U_SIGN3P.2, J_STRADDLE_EDGE.A17, J_STRADDLE_EDGE.A18, J_STRADDLE_EDGE.A19, J_STRADDLE_EDGE.A20, J_STRADDLE_EDGE.A21, J_STRADDLE_EDGE.A22, J_STRADDLE_EDGE.A23, J_STRADDLE_EDGE.A24, J_STRADDLE_EDGE.A25, J_STRADDLE_EDGE.A26, J_STRADDLE_EDGE.A27, J_STRADDLE_EDGE.A28, J_STRADDLE_EDGE.A29, J_STRADDLE_EDGE.A30, J_STRADDLE_EDGE.A31, J_STRADDLE_EDGE.A32, J_STRADDLE_EDGE.A33, J_STRADDLE_EDGE.A34, J_STRADDLE_EDGE.A35, J_STRADDLE_EDGE.A36, J_STRADDLE_EDGE.A37, J_STRADDLE_EDGE.A38, J_STRADDLE_EDGE.B11, J_STRADDLE_EDGE.B12, J_STRADDLE_EDGE.B13, J_STRADDLE_EDGE.B14, J_STRADDLE_EDGE.B15, J_STRADDLE_EDGE.B16, J_STRADDLE_EDGE.B17, J_STRADDLE_EDGE.B18, J_STRADDLE_EDGE.B19, J_STRADDLE_EDGE.B20, J_STRADDLE_EDGE.B21, J_STRADDLE_EDGE.B22, J_STRADDLE_EDGE.B23, J_STRADDLE_EDGE.B24, J_STRADDLE_EDGE.B25, J_STRADDLE_EDGE.B26, J_STRADDLE_EDGE.B27, J_STRADDLE_EDGE.B28, J_STRADDLE_EDGE.B29, J_STRADDLE_EDGE.B30, J_STRADDLE_EDGE.B31, J_STRADDLE_EDGE.B32, R_LED_0.2, R_LED_1.2, R_LED_2.2, R_LED_3.2, R_LED_4.2, R_LED_5.2, R_LED_6.2, R_LED_7.2, R_LED_8.2, R_LED_9.2, U1.3, U1.5, U1.10, U1.12, U2.3, U2.5, U2.10, U2.12, U3.3, U3.5, U3.10, U3.12, U_SIGN1.3, U_SIGN1.5, U_SIGN1.10, U_SIGN1.12, U_SIGN2.3, U_SIGN2.5, U_SIGN2.10, U_SIGN2.12, U_SIGN3.3, U_SIGN3.5, U_SIGN3.10, U_SIGN3.12
INV_L2_0: R2_0_0.2, R2_3_0.2, R2_4_0.2, R2_5_0.2, R2_6_0.2, R2_7_0.2, R2_9_0.2, R2_10_0.2, R2_12_0.2, R2_13_0.2, R2_14_0.2, R2_15_0.2, R_SIGN_IN_0.2, Rb_L2_0.2, Rf_L2_0.1, U1.2
INV_L2_1: R2_1_1.2, R2_2_1.2, R2_3_1.2, R2_6_1.2, R2_8_1.2, R2_10_1.2, R2_12_1.2, R2_14_1.2, R_SIGN_IN_1.2, Rb_L2_1.2, Rf_L2_1.1, U1.6
INV_L2_2: R2_0_2.2, R2_2_2.2, R2_5_2.2, R2_6_2.2, R2_7_2.2, R2_8_2.2, R2_9_2.2, R2_11_2.2, R_SIGN_IN_2.2, Rb_L2_2.2, Rf_L2_2.1, U2.2
INV_L2_3: R2_1_3.2, R2_4_3.2, R2_8_3.2, R2_9_3.2, R2_12_3.2, R2_14_3.2, R_SIGN_IN_3.2, Rb_L2_3.2, Rf_L2_3.1, U2.6
INV_L2_4: R2_0_4.2, R2_2_4.2, R2_3_4.2, R2_4_4.2, R2_6_4.2, R2_7_4.2, R2_8_4.2, R2_10_4.2, R_SIGN_IN_4.2, Rb_L2_4.2, Rf_L2_4.1, U3.2
INV_L2_5: R2_0_5.2, R2_1_5.2, R2_3_5.2, R2_5_5.2, R2_10_5.2, R2_12_5.2, R2_13_5.2, R_SIGN_IN_5.2, Rb_L2_5.2, Rf_L2_5.1, U3.6
INV_L2_6: R2_0_6.2, R2_2_6.2, R2_3_6.2, R2_4_6.2, R2_5_6.2, R2_8_6.2, R2_10_6.2, R2_11_6.2, R2_14_6.2, R_SIGN_IN_6.2, Rb_L2_6.1, Rf_L2_6.2, U1.13
INV_L2_7: R2_1_7.2, R2_2_7.2, R2_5_7.2, R2_6_7.2, R2_7_7.2, R2_12_7.2, R_SIGN_IN_7.2, Rb_L2_7.1, Rf_L2_7.2, U1.9
INV_L2_8: R2_0_8.2, R2_1_8.2, R2_3_8.2, R2_4_8.2, R2_9_8.2, R2_10_8.2, R2_13_8.2, R2_14_8.2, R2_15_8.2, R_SIGN_IN_8.2, Rb_L2_8.1, Rf_L2_8.2, U2.13
INV_L2_9: R2_1_9.2, R2_3_9.2, R2_4_9.2, R2_6_9.2, R2_7_9.2, R2_9_9.2, R2_10_9.2, R2_11_9.2, R2_12_9.2, R2_13_9.2, R_SIGN_IN_9.2, Rb_L2_9.1, Rf_L2_9.2, U2.9
LED_N_0: D_LED_0.2, R_LED_0.1
LED_N_1: D_LED_1.2, R_LED_1.1
LED_N_2: D_LED_2.2, R_LED_2.1
LED_N_3: D_LED_3.2, R_LED_3.1
LED_N_4: D_LED_4.2, R_LED_4.1
LED_N_5: D_LED_5.2, R_LED_5.1
LED_N_6: D_LED_6.2, R_LED_6.1
LED_N_7: D_LED_7.2, R_LED_7.1
LED_N_8: D_LED_8.2, R_LED_8.1
LED_N_9: D_LED_9.2, R_LED_9.1
NC_U3_8: U3.8, U3.9
NC_U3_14: U3.13, U3.14
NC_U_SIGN3_8: U_SIGN3.8, U_SIGN3.9
NC_U_SIGN3_14: U_SIGN3.13, U_SIGN3.14
POS_GROUP_0: R_SIGN_FB_0.1, R_SIGN_IN_0.1, U_SIGN1.1
POS_GROUP_1: R_SIGN_FB_1.1, R_SIGN_IN_1.1, U_SIGN1.7
POS_GROUP_2: R_SIGN_FB_2.1, R_SIGN_IN_2.1, U_SIGN1.8
POS_GROUP_3: R_SIGN_FB_3.1, R_SIGN_IN_3.1, U_SIGN1.14
POS_GROUP_4: R_SIGN_FB_4.1, R_SIGN_IN_4.1, U_SIGN2.1
POS_GROUP_5: R_SIGN_FB_5.1, R_SIGN_IN_5.1, U_SIGN2.7
POS_GROUP_6: R_SIGN_FB_6.1, R_SIGN_IN_6.1, U_SIGN2.8
POS_GROUP_7: R_SIGN_FB_7.1, R_SIGN_IN_7.1, U_SIGN2.14
POS_GROUP_8: R_SIGN_FB_8.1, R_SIGN_IN_8.1, U_SIGN3.1
POS_GROUP_9: R_SIGN_FB_9.1, R_SIGN_IN_9.1, U_SIGN3.7
POS_INV_0: R2_1_0.2, R2_2_0.2, R2_8_0.2, R2_11_0.2, R_SIGN_FB_0.2, U_SIGN1.2
POS_INV_1: R2_0_1.2, R2_4_1.2, R2_5_1.2, R2_7_1.2, R2_9_1.2, R2_11_1.2, R2_13_1.2, R2_15_1.2, R_SIGN_FB_1.2, U_SIGN1.6
POS_INV_2: R2_1_2.2, R2_3_2.2, R2_4_2.2, R2_10_2.2, R2_12_2.2, R2_13_2.2, R2_14_2.2, R2_15_2.2, R_SIGN_FB_2.2, U_SIGN1.9
POS_INV_3: R2_0_3.2, R2_2_3.2, R2_3_3.2, R2_5_3.2, R2_6_3.2, R2_7_3.2, R2_10_3.2, R2_11_3.2, R2_13_3.2, R2_15_3.2, R_SIGN_FB_3.2, U_SIGN1.13
POS_INV_4: R2_1_4.2, R2_5_4.2, R2_9_4.2, R2_11_4.2, R2_12_4.2, R2_13_4.2, R2_14_4.2, R2_15_4.2, R_SIGN_FB_4.2, U_SIGN2.2
POS_INV_5: R2_2_5.2, R2_4_5.2, R2_6_5.2, R2_7_5.2, R2_8_5.2, R2_9_5.2, R2_11_5.2, R2_14_5.2, R2_15_5.2, R_SIGN_FB_5.2, U_SIGN2.6
POS_INV_6: R2_1_6.2, R2_6_6.2, R2_7_6.2, R2_9_6.2, R2_12_6.2, R2_13_6.2, R2_15_6.2, R_SIGN_FB_6.2, U_SIGN2.9
POS_INV_7: R2_0_7.2, R2_3_7.2, R2_4_7.2, R2_8_7.2, R2_9_7.2, R2_10_7.2, R2_11_7.2, R2_13_7.2, R2_14_7.2, R2_15_7.2, R_SIGN_FB_7.2, U_SIGN2.13
POS_INV_8: R2_2_8.2, R2_5_8.2, R2_6_8.2, R2_7_8.2, R2_8_8.2, R2_11_8.2, R2_12_8.2, R_SIGN_FB_8.2, U_SIGN3.2
POS_INV_9: R2_0_9.2, R2_2_9.2, R2_5_9.2, R2_8_9.2, R2_14_9.2, R2_15_9.2, R_SIGN_FB_9.2, U_SIGN3.6
SCORE_0: D_LED_0.1, D_WTA_0.2, J_STRADDLE_EDGE.B1, Rf_L2_0.2, U1.1
SCORE_1: D_LED_1.1, D_WTA_1.2, J_STRADDLE_EDGE.B2, Rf_L2_1.2, U1.7
SCORE_2: D_LED_2.1, D_WTA_2.2, J_STRADDLE_EDGE.B3, Rf_L2_2.2, U2.1
SCORE_3: D_LED_3.1, D_WTA_3.2, J_STRADDLE_EDGE.B4, Rf_L2_3.2, U2.7
SCORE_4: D_LED_4.1, D_WTA_4.2, J_STRADDLE_EDGE.B5, Rf_L2_4.2, U3.1
SCORE_5: D_LED_5.1, D_WTA_5.2, J_STRADDLE_EDGE.B6, Rf_L2_5.2, U3.7
SCORE_6: D_LED_6.1, D_WTA_6.2, J_STRADDLE_EDGE.B7, Rf_L2_6.1, U1.14
SCORE_7: D_LED_7.1, D_WTA_7.2, J_STRADDLE_EDGE.B8, Rf_L2_7.1, U1.8
SCORE_8: D_LED_8.1, D_WTA_8.2, J_STRADDLE_EDGE.B9, Rf_L2_8.1, U2.14
SCORE_9: D_LED_9.1, D_WTA_9.2, J_STRADDLE_EDGE.B10, Rf_L2_9.1, U2.8
WTA_BUS: D_WTA_0.1, D_WTA_1.1, D_WTA_2.1, D_WTA_3.1, D_WTA_4.1, D_WTA_5.1, D_WTA_6.1, D_WTA_7.1, D_WTA_8.1, D_WTA_9.1, R_WTA.1
